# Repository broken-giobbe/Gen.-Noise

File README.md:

# Gen.-Noise
IoT random number generator

## Firmware
**TODO:** explain firmware here

## Board & Schematics
Requires
[Kicad tools for Wemos D1 mini](https://github.com/jerome-labidurie/d1_mini_kicad)
for the D1 mini symbol and PCB footprint.

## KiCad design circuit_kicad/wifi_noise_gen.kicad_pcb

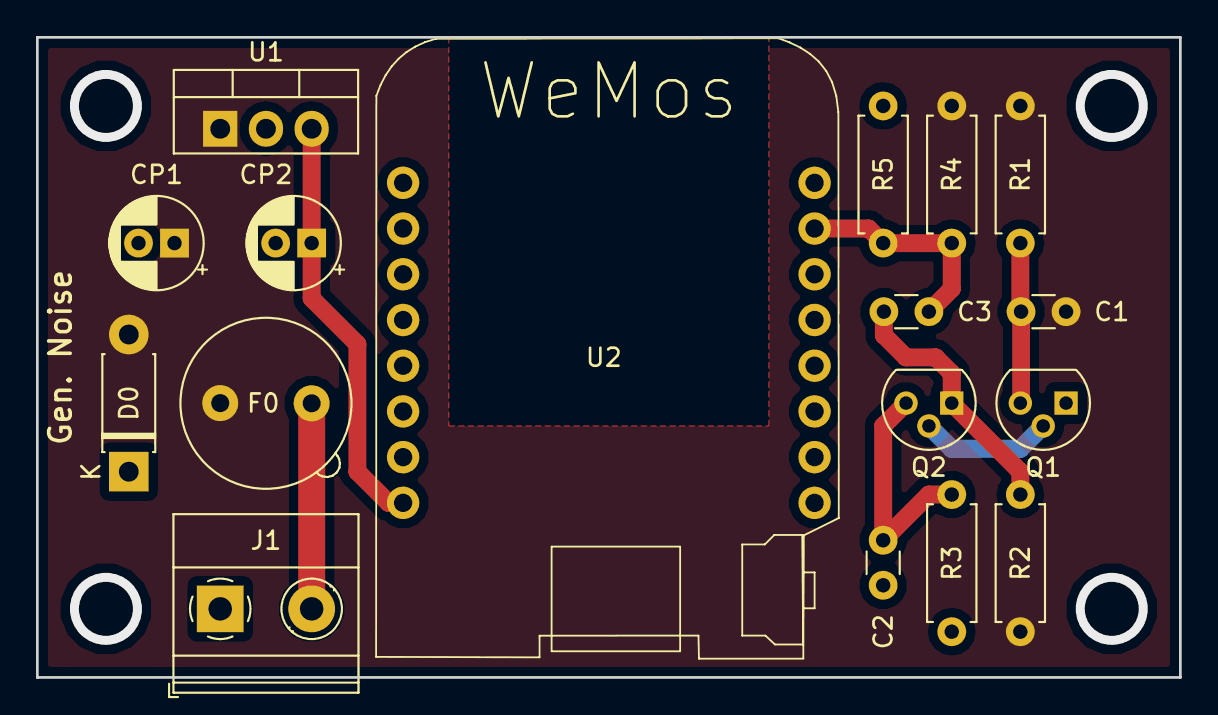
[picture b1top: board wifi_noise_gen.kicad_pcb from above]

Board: 2 copper layers, 63.5 x 35.6 mm, 17 parts (0 on the bottom side), 9 nets.

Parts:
C1, C2, C3: 0.1u; C_Disc_D3.0mm_W1.6mm_P2.50mm
CP1, CP2: CP; CP_Radial_D5.0mm_P2.00mm
D0: 1n400x; D_DO-41_SOD81_P7.62mm_Horizontal
F0: 0.5A; Fuseholder_TR5_Littelfuse_No560_No460
J1: Screw_Terminal_01x02; TerminalBlock_Phoenix_MKDS-1,5-2-5.08_1x02_P5.08mm_Horizont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
Q1, Q2: Q_NPN; TO-92
R1: 470k; R_Axial_DIN0207_L6.3mm_D2.5mm_P7.62mm_Horizontal
R2: 4.7k; R_Axial_DIN0207_L6.3mm_D2.5mm_P7.62mm_Horizontal
R3: 1k; R_Axial_DIN0207_L6.3mm_D2.5mm_P7.62mm_Horizontal
R4, R5: R?; R_Axial_DIN0207_L6.3mm_D2.5mm_P7.62mm_Horizontal
U1: L7805; TO-220-3_Vertical
U2: WeMos_mini; D1_mini_board

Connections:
+5V: CP2.1, U1.3, U2.1
+12V: C1.1, CP1.1, D0.2, F0.1, R1.1, R2.1, R4.1, U1.1
GND: C2.2, CP1.2, CP2.2, D0.1, J1.1, R3.2, R5.2, U1.2, U2.2
unnamed: C1.2, Q1.3, R1.2
unnamed: C2.1, Q2.3, R3.1
unnamed: C3.2, Q2.1, R2.2
unnamed: F0.2, J1.2
unnamed: Q1.2, Q2.2
Vnoise: C3.1, R4.2, R5.1, U2.10

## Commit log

2019-02-26 Add initial firmware
    It's ugly but it (kind of) works
2019-02-27 Add schematic and PCB layout
2020-03-21 Make the arduino IDE happy by moving firmware file into their folder
